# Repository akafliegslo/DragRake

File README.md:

# Drag Rake
## Project Overview

Drag Rake is an integrating drag measuring rake with a universal attachment mechanism for all wings and a modern, wireless solution that records and displays drag data to the cockpit in real-time created by [Akaflieg SLO](akslo.com). A drag rake is composed of a series of pneumatic tubes that sample the air pressure of the wing wake. By knowing the wake air pressure and the undisturbed air pressure, a good estimate of the wing drag can be determined. Our drag rake is unique in that all the electronics are contained on the rake itself, as opposed to existing drag rake systems where the electronics are inside of the aircraft away from the drag rake. A self-contained unit significantly reduces the set-up time since the system is portable and only needs to be mounted to the wing; unlike traditional systems, pneumatic tubing does not need to be run from the drag rake to the interior of the aircraft. Our drag rake relays data to the pilot in real-time via an IoT WiFi equipped microcontroller that can send the data to any smart device with a web browser.

This repository contains all the drawings, CAD files, PCB files, code, and guides for how to build our particular drag rake. In the spirit of the open-source community, every part of this project is open-source and free to use. All feedback and improvements are appreciated!

### Drag Rake Pneumatic System Overview
Like other drag measuring rakes, Drag Rake measures and compares the head pressure in the freestream and wing wake. A series of tubes parallel to the approximate local flow vertically oriented at the trailing edge of the wing collect the in-wake head pressure and a common plenum chamber connected to these tubes provides an average of the head pressure. Another tube also parallel to the flow, but sticking out from the wing, as to avoid its influence, provides freestream head pressure. The wake head and freestream head are compared by a highly accurate digital differential pressure transducer. Since the upper surface and lower surface of the wing have different localized pressures, there are two sets of wake head and freestream head tubes and differential pressure sensors, one set for each side of the wing.  

### Electrical System Overview
Pressure values from the pressure sensors are read by a microcontroller via the SPI digital protocol. Measurement commands are sent to each sensor and are then read back by the microcontroller. These pressure sensors have multiple kinds of measurement commands (single read and average of 2, 4, 8 or 16 reads), but testing will need to be conducted to see if one kind of read is better (more accurate, less noise, etc.). Also on the SPI bus are the SD card for data logging and the integrated WiFi module. 

Power to the system is provided by a 400 mAh battery that is kept underneath the microcontroller. Power to the SD card and pressure sensors comes from the battery via the microcontroller and 3.3V line.

### Wireless System Overview
In order to ensure that a wide range of devices could wirelessly connect to Drag Rake, an agnotistic wireless connection scheme was developed by using a WiFi-equipped microcontroller. The microcontroller creates a wireless network and hosts a webpage that displays the data from Drag Rake in real time. An agnostic WiFi-equipped device can then connect to the network, find the webpage's IP address, and display the data in real time (updates automatically, no refreshing necessary). 

## Current Tasks
- [x] Implement SD card data logging
- [x] Convert from I2C data bus to SPI data bus
- [ ] Software testing
- [ ] Publish polished code to master! :shipit: 
- [x] PCB redesign for SPI
- [x] Create drawings from CAD for manufacturing
- [x] Create BOM for DIYers
- [ ] Create build guide for DIYers
- [ ] Whitepaper on wireless interface

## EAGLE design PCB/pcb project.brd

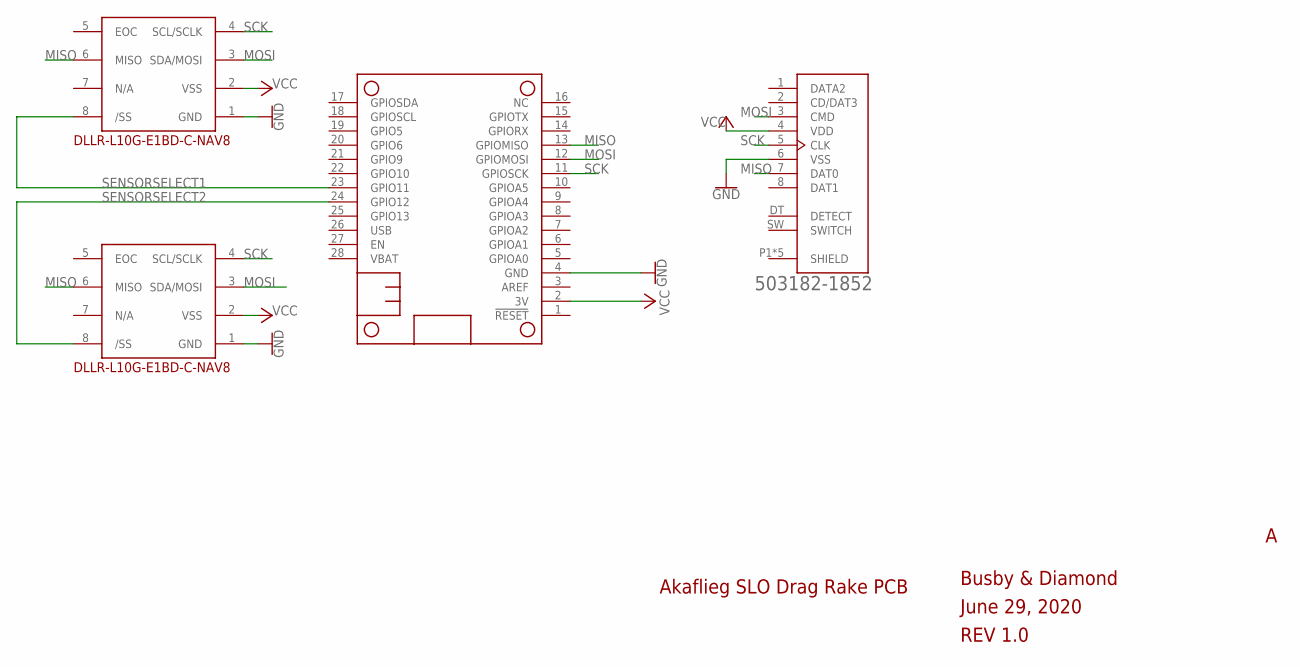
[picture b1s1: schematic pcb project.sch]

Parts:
DLLR-L10G-E1BD-C-NAV8_BOT: DLLR-L10G-E1BD-C-NAV8_BOT; DLLR-L10G-E1BD-C-NAV8
DLLR-L10G-E1BD-C-NAV8_TOP: DLLR-L10G-E1BD-C-NAV8_TOP; DLLR-L10G-E1BD-C-NAV8
MS1: FEATHERWING
SD_CARD: 503182-1852; MOLEX_503182-1852

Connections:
GND: DLLR-L10G-E1BD-C-NAV8_BOT.1 (GND), DLLR-L10G-E1BD-C-NAV8_TOP.1 (GND), MS1.4 (GND), SD_CARD.6 (VSS)
MISO: DLLR-L10G-E1BD-C-NAV8_BOT.6 (MISO), DLLR-L10G-E1BD-C-NAV8_TOP.6 (MISO), MS1.13 (GPIOMISO), SD_CARD.7 (DAT0)
MOSI: DLLR-L10G-E1BD-C-NAV8_BOT.3 (SDA/MOSI), DLLR-L10G-E1BD-C-NAV8_TOP.3 (SDA/MOSI), MS1.12 (GPIOMOSI), SD_CARD.3 (CMD)
SCK: DLLR-L10G-E1BD-C-NAV8_BOT.4 (SCL/SCLK), DLLR-L10G-E1BD-C-NAV8_TOP.4 (SCL/SCLK), MS1.11 (GPIOSCK), SD_CARD.5 (CLK)
SENSORSELECT1: DLLR-L10G-E1BD-C-NAV8_TOP.8 (/SS), MS1.23 (GPIO11)
SENSORSELECT2: DLLR-L10G-E1BD-C-NAV8_BOT.8 (/SS), MS1.24 (GPIO12)
VCC: DLLR-L10G-E1BD-C-NAV8_BOT.2 (VSS), DLLR-L10G-E1BD-C-NAV8_TOP.2 (VSS), MS1.2 (3V), SD_CARD.4 (VDD)

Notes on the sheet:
June 29, 2020
Akaflieg SLO Drag Rake PCB
Busby & Diamond
REV 1.0

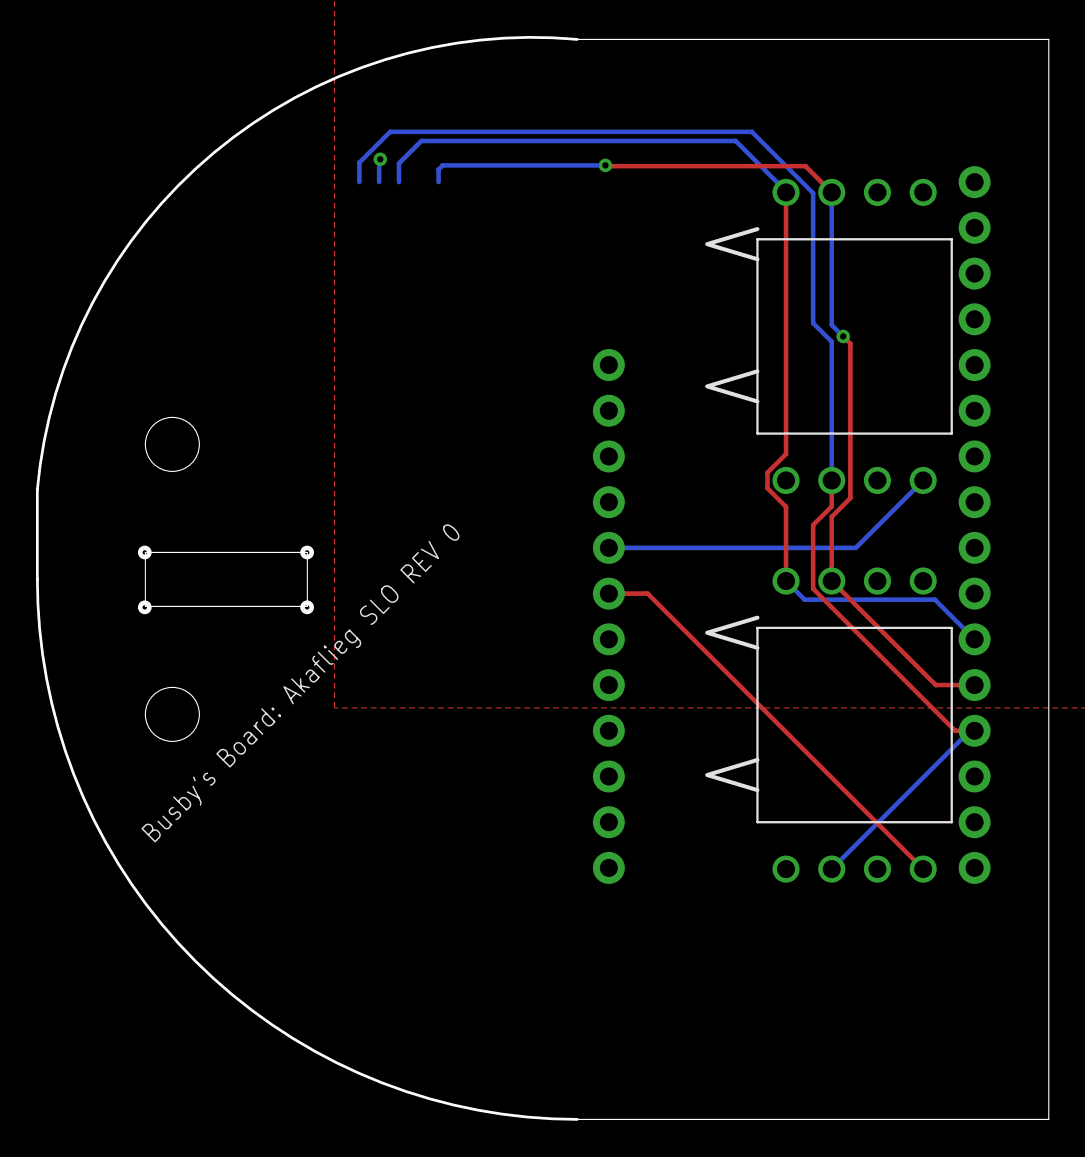
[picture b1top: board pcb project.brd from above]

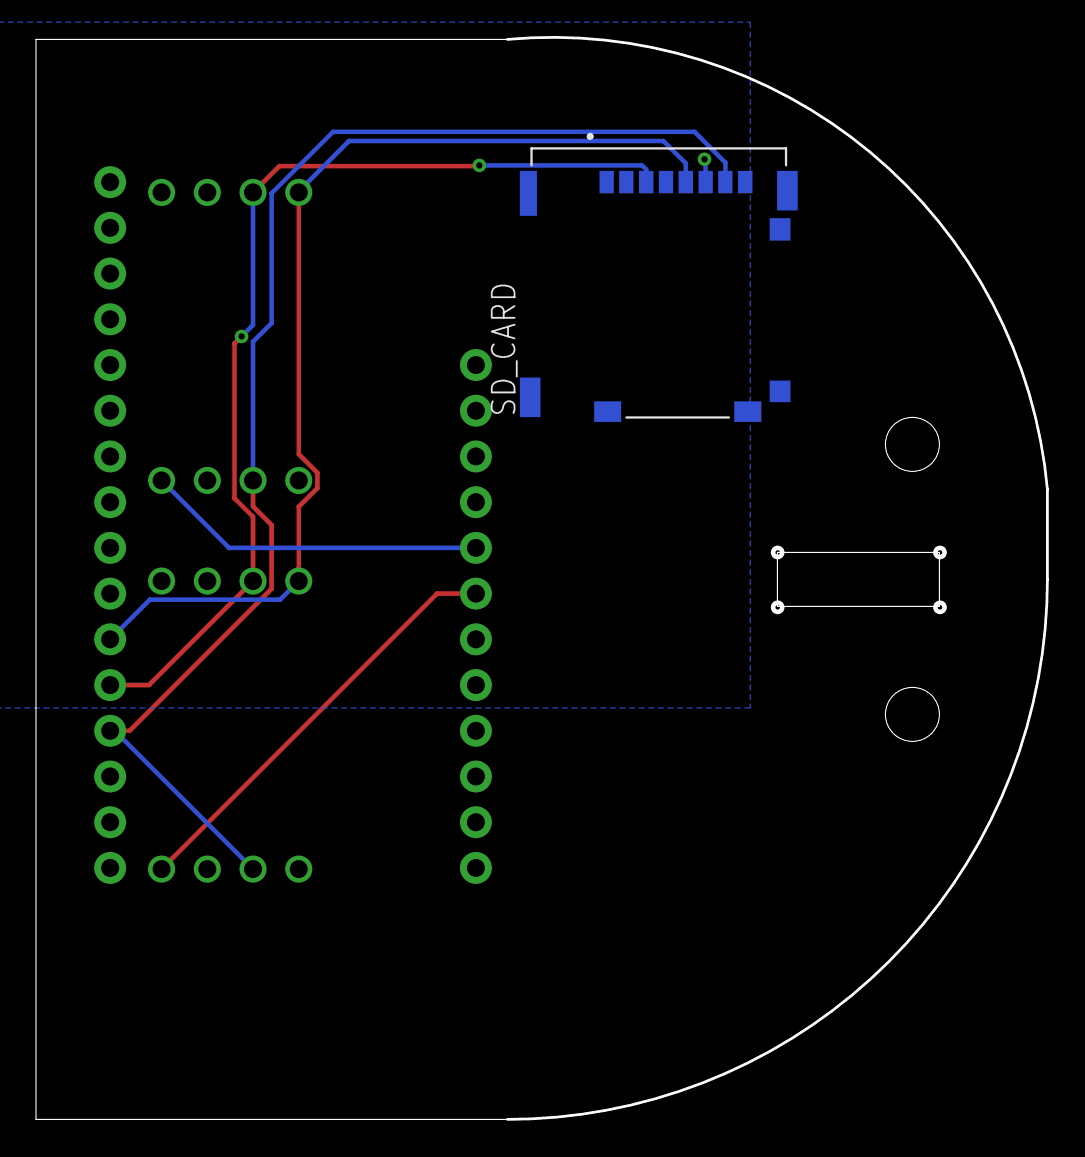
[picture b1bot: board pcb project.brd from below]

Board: 2 copper layers, 56.0 x 60.0 mm, 4 parts (2 on the bottom side), 7 nets.

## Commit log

2019-10-23 Added I2C code
    Separate file as the code has not been put together yet. The I2C code can output raw pressure data to a graph using the serial plotter.
2019-11-02 Added the WIP webpage
    There's still a lot of work to be done on it, but at least for now it can read the values from human input, display which mode is selected, and (very soon) can change the mode in which the transducer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
    I'll work on writing some more comments and documentation for the code in a bit, but right now I'm tired and could use a break :)
2019-11-02 Removed I2C stuff that may kill transducers
2019-11-02 Commented code that may kill transducers
2019-11-02 Missed some code
2019-11-03 Added combined code`
    Basically everything has been added to this code. All that needs to happen is to get the calculations right for the sensors, and make the two sensor system work.
2019-11-03 Renamed to get rid of confusion
2019-11-09 Integrated dual sensor operation with a scaled output
    Still needs to have conversion from (what I hope is) inches of water to knots. Other than that, everything is done.
    Has a bug: Clicking the buttons can cause the website to crash. Most likely this has something to do with the client requests not being read while the sensors are being polled.
2019-11-21 Added newest code
2020-01-09 Added PCB files
    REV A
2020-02-18 Added comments to code
    Also spaced it out and made it look nicer
2020-02-18 Old code clean up!
2020-02-18 MOAR old code clean up
2020-02-18 git has a steep learning curve
2020-02-18 BYE FELICIA
2020-02-18 Rename AKSLO_website/AKSLO_website.ino to main_code/AKSLO_website.ino
    Slightly nicer this way
2020-02-19 Added PCB files (#2)
    Just trying to make the PCB branch pretty
2020-02-20 Trying to make arduino less upset
2020-02-20 Adding stuff to make my local directory neat
2020-02-20 Create README.md
    Basic README, will need more details and documentation when I have the time
2020-02-21 Update README.md
    It's annoying that I need to commit every time ugh
2020-02-23 Added basic Sd card functionality
2020-02-23 Some small changes to make the compiler happier
2020-05-15 Removed velocity calc, is toggle() a command?
2020-05-15 made some small changes, still shouldn't work
2020-05-20 Added SD card support, complies
2020-05-26 Data logging made independent of WiFi connection
2020-05-26 Start of ESP32 port
2020-05-27 Created nice webpage (probs), rewrote SD esp. for ESP32, does the SD need to be different from the original? idk, might need to make changes to SPI for ESP32 specific
2020-06-03 Checkpoint: needs webpage formating fixed, parse data into buttons
2020-06-04 split SPI transfer on requestread to appease ESP32
2020-06-15 commiting so i can push everything to github
2020-08-06 Finalized PCB design + wind tunnel analysis, MCU code still a mess
2020-08-06 Cleaned up code, should compile, still broken
2020-08-06 Whoops, forgot to update the readme, lots of things are getting done!
2020-09-19 It compiles, still can't read sensors

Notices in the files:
parts and their libraries:
SparkFun-PowerSymbols: Licensing: Creative Commons ShareAlike 4.0 International - https://creativecommons.org/licenses/by-sa/4.0
